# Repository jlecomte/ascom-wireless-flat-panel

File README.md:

# ASCOM-Compatible Wireless Flat Panel

I do not charge anything to create and maintain these open-source projects. But if you would like to say "thanks" for this project, feel free to send any amount through Paypal using the button below. I appreciate your support!

* [Introduction](#introduction)
* [Finished Product](#finished-product)
* [User Manual](#user-manual)
* [Pre-Requisites](#pre-requisites)
* [Hardware](#hardware)
* [Bill Of Material](#bill-of-material)
* [ASCOM Driver](#ascom-driver)
  + [Downloading And Installing The Driver](#downloading-and-installing-the-driver)
  + [Compiling The Driver (For Developers Only)](#compiling-the-driver-for-developers-only)
* [Arduino Firmware](#arduino-firmware)
  + [Microcontroller Compatibility](#microcontroller-compatibility)
  + [Compiling And Uploading The Firmware](#compiling-and-uploading-the-firmware)
* [Electronic Circuit](#electronic-circuit)
  + [Schematics](#schematics)
  + [Breadboard Prototyping](#breadboard-prototyping)
  + [PCB](#pcb)
* [Mechanical Components And Assembly](#mechanical-components-and-assembly)
* [Troubleshooting](#troubleshooting)
  + [Changing the 3D model parameters to fit small telescopes](#changing-the-3d-model-parameters-to-fit-small-telescopes)
* [Frequently Asked Questions (FAQ)](#frequently-asked-questions-faq)

## Introduction

This project is the second iteration of my original DIY [ASCOM-compatible flat panel](https://github.com/jlecomte/ascom-flat-panel). It brings a major usability improvement over the first version: It is completely wireless! (whereas the first version relied on a USB type C and a 12V DC cable...) which makes it even easier to use, especially in the dark! It has several other enhancements compared to the original version, and I invite you to check out this video to find out more:

## Finished Product

## User Manual

Upon turning on the device, the indicator LEDs will show the battery voltage status. After 5 seconds, only the red LED will remain in use, indicating whether a device is currently connected: it will be solid on if a device is connected, or it will continuously blink otherwise.

Before you can connect to the wireless flat panel for the first time, you must select the appropriate device and open the device settings dialog. Here is what that looks like in N.I.N.A.:

In the device settings dialog, you must then select the appropriate Bluetooth device. The driver will remember your selection, so this is a one-time operation. This step is necessary to ensure that, in the field, where there may be several such wireless flat panels nearby, you are connecting and controlling the right device. Here is what the driver settings dialog looks like the first time you open it. It listens for Bluetooth advertisement packets coming from wireless flat panel devices only.

Of course, the Bluetooth address will be meaningless to you, but that is not important. Click on a Bluetooth address, and click on the "Pair with selected device" button:

**Note:** This is not really Bluetooth pairing. It is merely device selection. But most users are familiar with the "Bluetooth pairing" terminology, so I used it, even if it is not perfectly accurate from a technical point of view.

Don't forget to validate your choice by clicking on the green checkmark button at the bottom of the device settings dialog! (otherwise, your selection will not be taken into account)

If you do this at home with only one wireless flat panel turned on, you should see only one Bluetooth address in the list, so that's easy. However, if you do this in the field, and there is another wireless flat panel nearby, you may see several Bluetooth addresses. Choose one, connect to it, and turn it on/off to identify which device you are connected to. If you happen to select the wrong device, disconnect from it, open the driver settings dialog again, and choose another Bluetooth address (you will have remembered the Bluetooth address you connected to on the first try...) Simple! Of course, it's easier to do this at home when there is only one device showing in the list... Once the right device has been selected, you can finally connect to it:

## Pre-Requisites

* A Windows computer (Windows 10 or newer)
* [Microsoft Visual Studio](https://visualstudio.microsoft.com/)
* [ASCOM Platform](https://ascom-standards.org/)
* [ASCOM Platform Developer Components](https://ascom-standards.org/COMDeveloper/Index.htm)
* [Arduino IDE](https://www.arduino.cc/en/software)
* [FreeCAD](https://www.freecadweb.org/), a free and open-source 3D parametric modeler. Make sure that you have the latest version installed!
* A 3D printer and a slicer (I use a Creality Ender 3 S1 Plus, and Ultimaker Cura)
* A few basic tools that any tinkerer must own, such as a breadboard, a soldering iron, etc.

## Hardware

* [Adafruit Feather nRF52840 Express](https://www.adafruit.com/product/4062)
* [Natural white 5V LED strip](https://www.amazon.com/dp/B08H51D8QV?tag=darkskygeek-20)
* [FQP30N06L](https://www.amazon.com/dp/B07WHSD3GJ?tag=darkskygeek-20) (logic-level MOSFET)
* An assortment of 1/4W resistors ([example](https://www.amazon.com/dp/B08FD1XVL6?tag=darkskygeek-20))
* An assortment of colored 5mm LEDs ([example](https://www.amazon.com/dp/B09XDMJ6KY?tag=darkskygeek-20))
* A small LiPo battery with a JST-PH 2mm connector ([example](https://www.amazon.com/gp/product/B07BTV3W87?tag=darkskygeek-20)) — The polarity of the connector may be incorrect, so be careful or you may fry the expensive Adafruit Feather board! See note below...
* [Taloya LED Flush Mount Ceiling Light](https://www.amazon.com/dp/B08GX81JB1?tag=darkskygeek-20) — We will take it apart to extract its background disk, Light Guiding Plate (LGP), and diffuser. If you are outside the US and cannot find this item, look for an LED ceiling light on AliExpress ([Here](https://www.aliexpress.us/item/3256804883844716.html) is one that *may* work, I have not verified it) If you go with a different option than the one I selected, you will likely have to make changes to the project, for which I will not be able to support you.
* [3mm thick white acrylic sheet](https://www.amazon.com/dp/B0D2GTXJR1?tag=darkskygeek-20) — We will use that to make the internal diffuser.
* [Rocker switch ON/OFF](https://www.amazon.com/dp/B07XD8J2PL?tag=darkskygeek-20)
* [Brass inserts for 3D printed parts](https://www.amazon.com/dp/B0BXD1YMNS?tag=darkskygeek-20)
* [Assortment of small metric screws, nuts, and washers](https://www.amazon.com/dp/B08JCKH31Q?tag=darkskygeek-20)
* 50mm-long M3 bolts, which you can buy from your local home center or from [McMaster-Carr](https://www.mcmaster.com/products/screws/system-of-measurement~metric/thread-size~m3/fastener-head-type~socket/material~stainless-steel-2/length~50-mm/)
* [Assortment of JST-XH connectors](https://www.amazon.com/dp/B01MCZE2HM?tag=darkskygeek-20)
* [Assortment of electrolytic capacitors](https://www.amazon.com/dp/B07PBQXQNQ?tag=darkskygeek-20)

The following items are technically optional, but highly recommended:

* [Bench Power Supply](https://www.amazon.com/dp/B07GCJ5QHF?tag=darkskygeek-20)
* [Solderless Breadboard](https://www.amazon.com/gp/product/B07LG9V8WQ?tag=darkskygeek-20)
* [Solderless LED strip connectors](https://www.amazon.com/dp/B0BLCQXSXH?tag=darkskygeek-20) — Useful for testing, but cannot be used in the finished product without making changes to the 3D model.

**Important note about the LED strip:** Pick a "natural white" LED strip. Stay away from "warm white" because you will run into some problems with your OIII filter (it does not emit enough in the blue part of the spectrum) or "cool white" because you will have similar issues, but with the H⍺ or SII filters (it does not emit enough in the red part of the spectrum). Also, stay away from so-called "high density" LED strips, they are simply too bright for our application. And finally, note that most LED strips require 12V DC, but in this project, we need one that can be powered with 5V DC. Actually, we are going to power the LED strip using 3.3V DC so that it is not too bright for our application.

**Important note about the LiPo battery:** Do _not_ connect the LiPo battery directly to the microcontroller board via the JST connector, unless you are certain about the battery's connector polarity. See the warning documented on [this Adafruit documentation page](https://learn.adafruit.com/introducing-the-adafruit-nrf52840-feather/power-management-2).

## Bill Of Material

Assuming that you already own a 3D printer, some basic equipment (e.g., a soldering iron), and some basic hardware and electronic components (an assortment of resistors and colored LEDs can be purchased in bulk and reused for a variety of projects — same for metric nuts and bolts or threaded inserts), here is the bill of materials (BOM) for this project (all prices are in USD and accurate as of January 2024):

* Adafruit Feather nRF52840 Express: **$25**
* LED strip: **$11**
* MOSFET: $10 for a pack of 10, so we will only count **$1** for this item in the BOM cost.
* LiPo battery: **$12**
* Taloya ceiling light: **$14**
* Switch: $9 for a pack of 10, so we will only count **$1** for this item in the BOM cost.
* White acrylic sheet: $24 for 3 12"x12" sheets, so we will only count **$8** for this item in the BOM cost.
* PCB manufacturing + shipping: $15 for 5 PCBs, so we will only count **$3** for this item in the BOM cost.
* Miscellaneous: JST connectors, capacitor, resistors, etc. These are so cheap that they do not contribute much to the BOM cost.

**Total cost ~ $75**

While this isn't exactly "cheap", it is significantly more affordable than a commercial unit. For example, PrimaLuceLab sells an excellent, albeit wired flat field generator named Giotto which, for a 6" refractor, costs **$315**. [Deep Sky Dad](https://deepskydad.com/) sells excellent _motorized_ flat panels, but they cost **$300** and up. This should help you decide whether this project is worth the effort.

## ASCOM Driver

### Downloading And Installing The Driver

You can install the ASCOM driver by simply running the executable setup file that you will find in the [releases page](https://github.com/jlecomte/ascom-wireless-flat-panel/releases). By default, it places files under `C:\Program Files (x86)\Dark Sky Geek\Wireless Flat Panel ASCOM Driver`.

### Compiling The Driver (For Developers Only)

Open Microsoft Visual Studio as an administrator (right click on the Microsoft Visual Studio shortcut, and select "Run as administrator"). This is required because when building the code, by default, Microsoft Visual Studio will register the compiled COM components, and this operation requires special privileges (Note: This is something you can disable in the project settings...) Then, open the solution (`ASCOM_Driver\WirelessFlatPanel.sln`), change the solution configuration to `Release` (in the toolbar), open the `Build` menu, and click on `Build Solution`. As long as you have properly installed all the required dependencies, the build should succeed and the ASCOM driver will be registered on your system. The binary file generated will be `ASCOM_Driver\bin\Release\ASCOM.DarkSkyGeek.WirelessFlatPanel.dll`. You may also download this file from the [Releases page](https://github.com/jlecomte/ascom-wireless-flat-panel/releases).

## Arduino Firmware

### Microcontroller Compatibility

The firmware was written specifically for, and tested with, an Adafruit Feather nRF52840 Express. It will likely not work on all Arduino-compatible boards. Please, do not file an issue if you encounter a problem with a different type of microcontroller board.

### Compiling And Uploading The Firmware

* Please, follow the [Arduino IDE setup steps](https://learn.adafruit.com/introducing-the-adafruit-nrf52840-feather/arduino-bsp-setup) published by Adafruit.
* Then, connect your Adafruit Feather nRF52840 Express board to your computer using a micro USB cable, open the sketch file located at `Arduino_Firmware\Arduino_Firmware.ino`, and click on the `Upload` button in the toolbar.

## Electronic Circuit

I included a [KiCad](https://www.kicad.org/) project in the `KiCad_Project/` directory.

### Schematics

The values of the resistors R1-R4 depend on the specific colored LEDs you are using. In my case, in order to have all the colored LEDs emit roughly the same brightness, I settled on the following values. You will have to experiment a bit to find out which values work best for you.

* `R1`: 2kΩ
* `R2`: 5kΩ
* `R3`: 1kΩ
* `R4`: 2kΩ

### Breadboard Prototyping

It is critical to prototype this circuit on a breadboard before ordering a PCB, or soldering the components on a perforated board. Here is what my prototype looked like:

### PCB

Here are 3D renderings of the PCB:

And here is a rendering of the various PCB layers:

I exported the Gerber files so that you can have the board manufactured by PCBWay (download the Gerber files for PCBWay [here](KiCad_Project/PCBWay.zip)). When you create your order with PCBWay, keep all the defaults, and set the board size to 66.5mm x 51.3mm. To keep the cost down, select the cheapest shipping method (to ship to the US, I select USPS) and consider doing a "group buy" with other people.

If you want to work with another PCB manufacturer, you will need to open the KiCad project and export the PCB layout to Gerber files. Please, follow the instructions of your PCB manufacturer. They all have slightly different requirements...

Here is a photograph of the control box, which hosts the PCB, after soldering all the components. Note how the switch has been wired.

The battery indicator LEDs protrude slightly on the other side of the control box:

## Mechanical Components And Assembly

If you are new to 3D modeling and 3D printing, take a look at [this video](https://www.youtube.com/watch?v=02CWCsGPJ-s) for a quick introduction.

You will need to print a number of parts. Use the 3D model I included in this repository ([`3D_Files/FreeCAD_Model.FCStd`](3D_Files/FreeCAD_Model.FCStd)) to generate STL files for your telescope. Simply open the 3D model in the most recent version of FreeCAD, click on the `Parameters` spreadsheet, and modify the OTA diameter and thickness values. The parametric model will automatically adapt to those values, and you will be able to export your own STL files, which you can then import into your slicer of choice.

In order to achieve good uniformity, this panel has two diffusers. The 3mm thick internal diffuser is made from a white acrylic sheet, and is located right underneath the spacer / right above the LGP. The external diffuser was extracted from the Tayola ceiling light.

To cut the LGP and the two diffusers cleanly and properly, I strongly recommend using a router table. The FreeCAD model contains 3 router templates, which you will need to print. Simply rough cut the component using a scroll saw (for example) and clean it up at the router table, using the appropriate template and a flush cut bit:

Please refer to this diagram to help you understand where the various components should be placed:

Solder flexible wires to the LED strip, and hot glue the connection (I used 5 minute epoxy) to ensure that they never work themselves loose... Then, install the LED strip into the body of the flat panel:

Install the background sheet and the LGP. It should be difficult to fit the LGP! The diodes on the LED strip must contact the side of the LGP, so it is normal and expected that it is a tight fit. I had to use a tiny screwdriver to ever so slightly pry the LED strip so I could push the LGP down all the way. Take your time, this is one of the most difficult operations!

Prepare the **internal diffuser**, which is made of a 3mm thick white acrylic sheet, and the spacer, and place them on top of the LGP:

Prepare the **external diffuser**, which you extracted from the Tayola ceiling light, and place it on top of the spacer:

Place the front on top of the external diffuser:

Install a JST connector for the LED leads, and connect the LED strip inside the control box:

**Note:** I used some foam padding to ensure that the battery was not going to move around.

All you have left to do is to fasten the flat panel using M3 bolts, washers, and nuts.

## Troubleshooting

### Changing the 3D model parameters to fit small telescopes

If you open the 3D model in FreeCAD and update the `OTA Outside Diameter` parameter to fit a much smaller telescope than this panel was originally designed for, you may get a `Recompute failed` error. This is because the minimum size of the panel is dictated by the length of the PCB. To fix this, set the `OTA Outside Diameter` parameter to a value larger than what you actually need, e.g., `130mm`, and increase the `OTA Thickness` parameter to a much larger value, e.g., `50mm` (in FreeCAD, you can make measurements using the `Draft` workbench to ensure that you have the proper value before printing any of the parts). The panel will be larger than what you actually need, but it will work. Play with the parameters and find what works for you.

## Frequently Asked Questions (FAQ)

**Question:** Can you make this for me? I'll pay for it!

**Answer:** I really wish I could. Unfortunately, I do not have the time necessary to manufacture this product for a large number of people.

**Question:** OK, I decided to build it, but I am stuck. Can you help me?

**Answer:** I will do my best, but I cannot provide any guarantee. Please, [file an issue](https://github.com/jlecomte/ascom-wireless-flat-panel/issues).

**Question:** Can you incorporate your DIY [ASCOM-compatible telescope cover](https://github.com/jlecomte/ascom-telescope-cover) into this project?

**Answer:** I am not interested in consolidating this project with my DIY [ASCOM-compatible telescope cover](https://github.com/jlecomte/ascom-telescope-cover) because, in my case, it would add too much weight to the front of my already front-heavy OTA, making it more difficult to balance, and causing all kinds of issues with the camera possibly hitting the tripod legs since the OTA would have to be moved back to provide proper balance. If you have a fully remote setup, I recommend looking at the excellent motorized flat panels sold by [Deep Sky Dad](https://deepskydad.com/). Otherwise, you can use a large and affordable LED tracing panel, which you can easily find on Amazon. Modify it to be ASCOM-compatible (see [this CloudyNights article](https://www.cloudynights.com/topic/536533-diy-alnitak-flat-panel/)), and position it vertically. Then, simply slew the telescope to it (the telescope will be in a horizontal position). Most modern Go-To mounts support storing several custom positions, so that makes it even easier! Anyway, you have a few options...

**Question:** Is this panel uniform enough?

**Answer:** Absolutely! Please refer to [my evaluation of the uniformity of this panel](https://github.com/jlecomte/circular-led-flat-panel-evaluation) for more information.

**Question:** Is this compatible with ZWO's ASIAir?

**Answer:** Unfortunately, no. As far as I know, ASIAir does not support ASCOM-compatible flat panels of any kind. That is because ASIAir is a closed ecosystem, and it is not possible to install additional drivers on an ASIAir unit. Additionally, ASIAir is based on the INDI platform, and I have not released an INDI driver for this device.

**Question:** My antivirus identifies your setup executable file as a malware (some kind of Trojan)

**Answer:** This is a false detection, extremely common with installers created with [Inno Setup](https://jrsoftware.org/isinfo.php) because virus and malware authors also use Inno Setup to distribute their malicious payload... Anyway, there isn't much I can do about this, short of signing the executable. Unfortunately, that would require a code signing certificate, which costs money. So, even though the executable I uploaded to GitHub is perfectly safe, use at your own risk!

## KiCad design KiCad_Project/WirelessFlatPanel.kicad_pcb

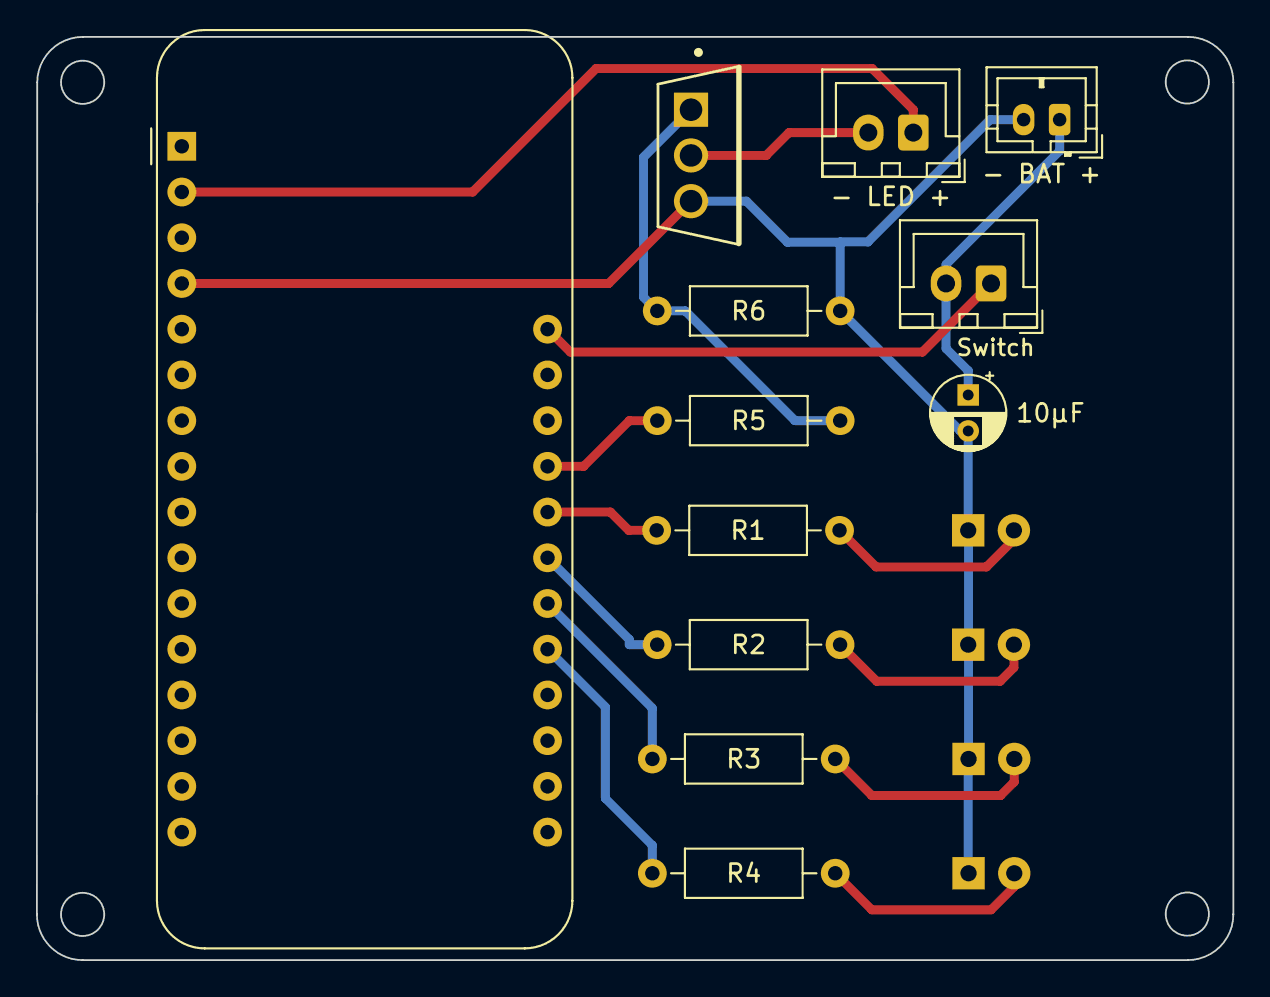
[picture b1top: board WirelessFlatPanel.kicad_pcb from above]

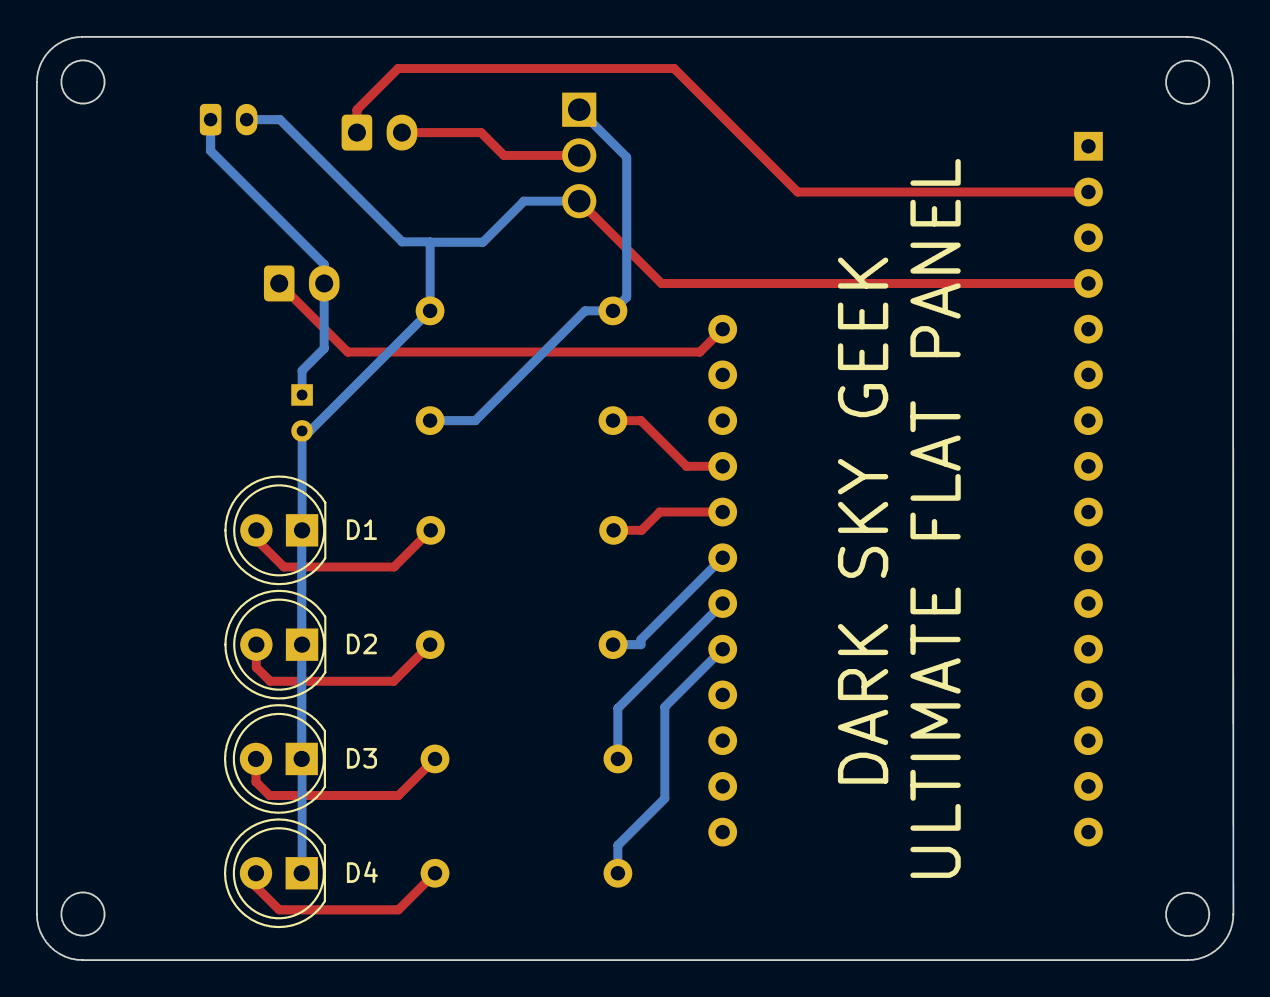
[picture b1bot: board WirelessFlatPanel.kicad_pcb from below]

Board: 2 copper layers, 66.5 x 51.3 mm, 16 parts (4 on the bottom side), 15 nets.

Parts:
10µF: 10µF; CP_Radial_D4.0mm_P2.00mm
- BAT +: JST-PH Bat; JST_PH_B2B-PH-K_1x02_P2.00mm_Vertical
- LED +: JST-XH LED; JST_XH_B2B-XH-A_1x02_P2.50mm_Vertical
A1: Adafruit Feather nRF52840 Express; Adafruit_Feather
D1, D2, D3, D4: LED; LED_D5.0mm
Q1: Val**; FQP30N06L
R1, R2, R3, R4, R5: 330Ω; R_Axial_DIN0207_L6.3mm_D2.5mm_P10.16mm_Horizontal
R6: 5KΩ; R_Axial_DIN0207_L6.3mm_D2.5mm_P10.16mm_Horizontal
Switch: JST-XH Switch; JST_XH_B2B-XH-A_1x02_P2.50mm_Vertical

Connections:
GND: 10µF.2, - BAT +.2, A1.4 (GND), D1.1 (K), D2.1 (K), D3.1 (K), D4.1 (K), Q1.3 (S), R6.1
unnamed: - LED +.1, A1.2 (3V3)
unnamed: A1.21 (D9), R4.2
unnamed: A1.22 (D10), R3.2
unnamed: A1.23 (D11), R2.2
unnamed: A1.24 (D12), R1.2
unnamed: A1.28 (VBAT), Switch.1
unnamed: 10µF.1, - BAT +.1, Switch.2
unnamed: D1.2 (A), R1.1
unnamed: D2.2 (A), R2.1
unnamed: D3.2 (A), R3.1
unnamed: D4.2 (A), R4.1
unnamed: Q1.1 (G), R5.1, R6.2
unnamed: - LED +.2, Q1.2 (D)
unnamed: A1.25 (D13), R5.2

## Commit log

2023-03-17 Lower PWM frequency to a more reasonable value
2023-03-19 Added ASCOM driver and license file
2023-03-19 Updated device name
2023-03-24 Added KiCad project
2023-03-27 Added images of PCB
2023-04-20 Simplification of the wireless flat panel
2023-04-20 Updated images
2023-04-20 Minor code refactoring
2023-04-20 Updated KiCad project to greatly simplify wiring
2023-04-21 Updated PCB footprint
2023-04-21 Updated FQP30N06 footprint
2023-04-24 Fixed a few minor details
2023-05-14 BLE characteristic can now take values 0-1023 for slightly better resolution
2023-11-05 Updated KiCad project
2023-11-05 Added FreeCAD model
2023-11-06 Updated 3D design and exported STL files for Askar 151PHQ
2023-11-06 Updated 3D model
2023-11-11 Updated README and 3D model
2023-11-19 Updated screenshot
2023-12-01 Updated behavior of indicator LEDs
2023-12-03 Use Inno Setup installer
2024-01-13 Added FAQ note about ASIAir
2024-01-13 Added capacitors to BOM
2024-01-13 Updated BOM
2024-01-14 Added PCBWay instructions
2024-01-14 Added note about Taloya's LED ceiling light availability
2024-01-17 Fixed a couple of issues reported
2024-03-10 Replaced char that is not properly displayed by the installer
2024-03-29 Added workaround for small telescopes
2024-09-25 Updated broken link

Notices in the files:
KiCad_Project/WirelessFlatPanel.kicad_pcb:
License: MIT
